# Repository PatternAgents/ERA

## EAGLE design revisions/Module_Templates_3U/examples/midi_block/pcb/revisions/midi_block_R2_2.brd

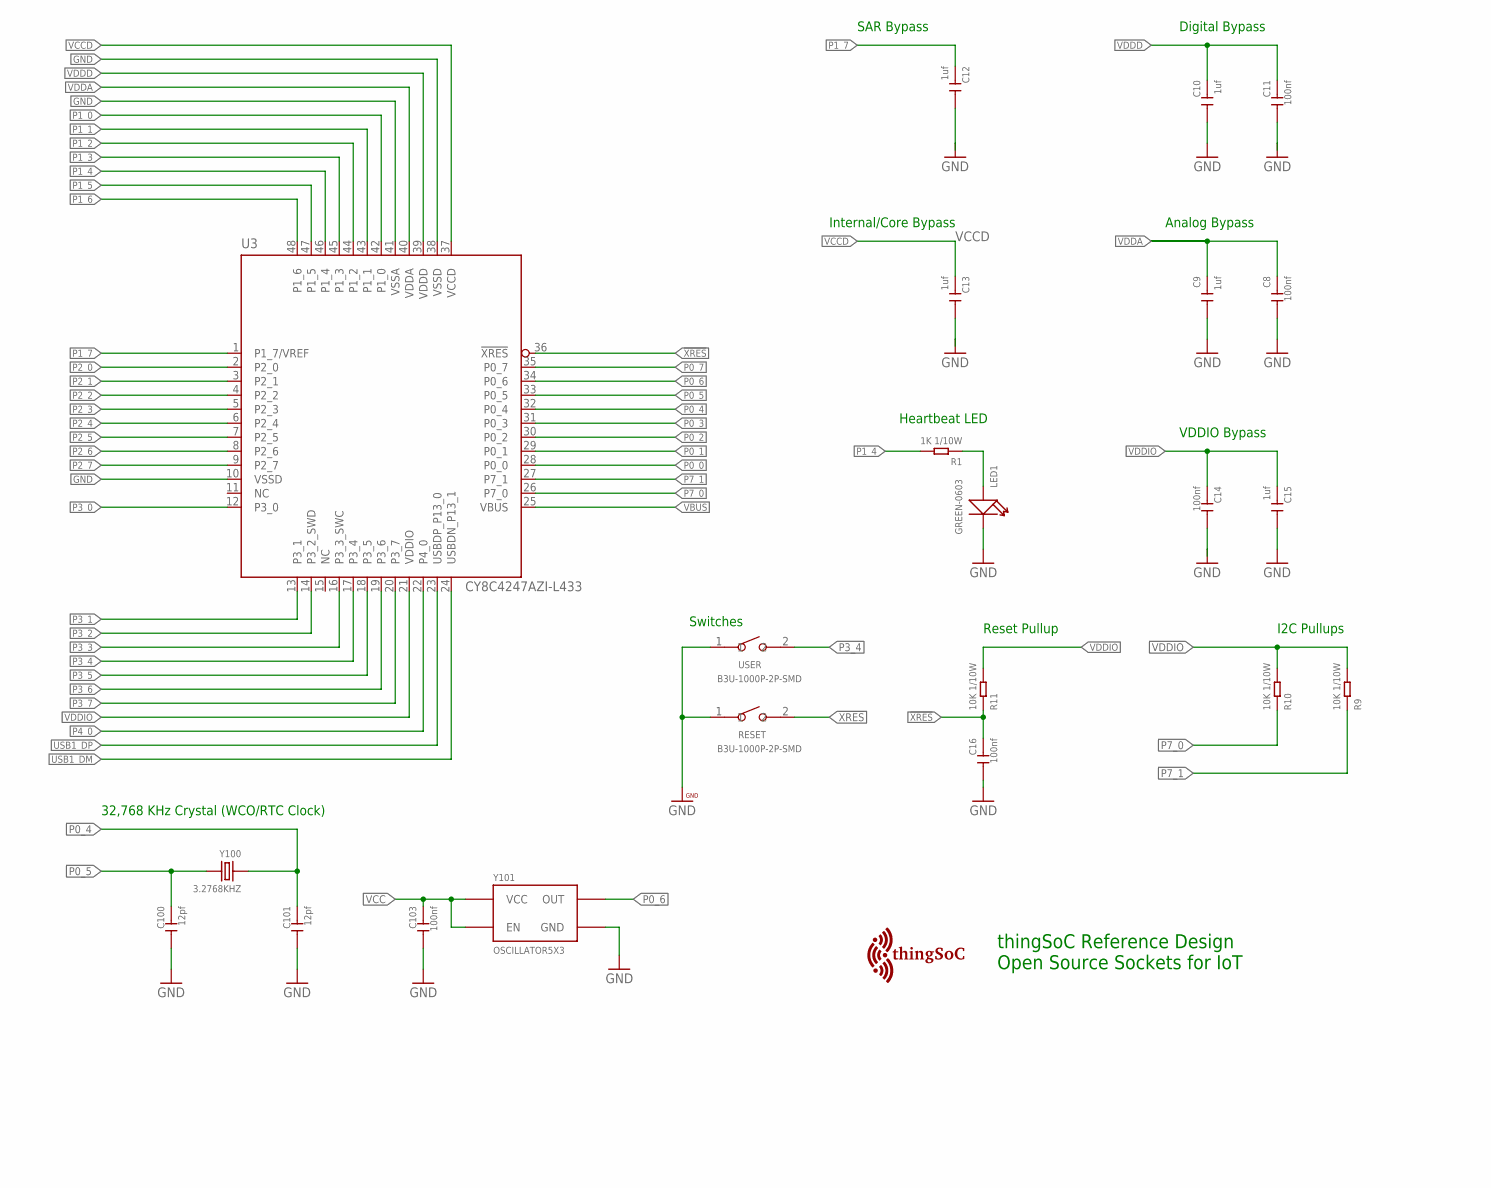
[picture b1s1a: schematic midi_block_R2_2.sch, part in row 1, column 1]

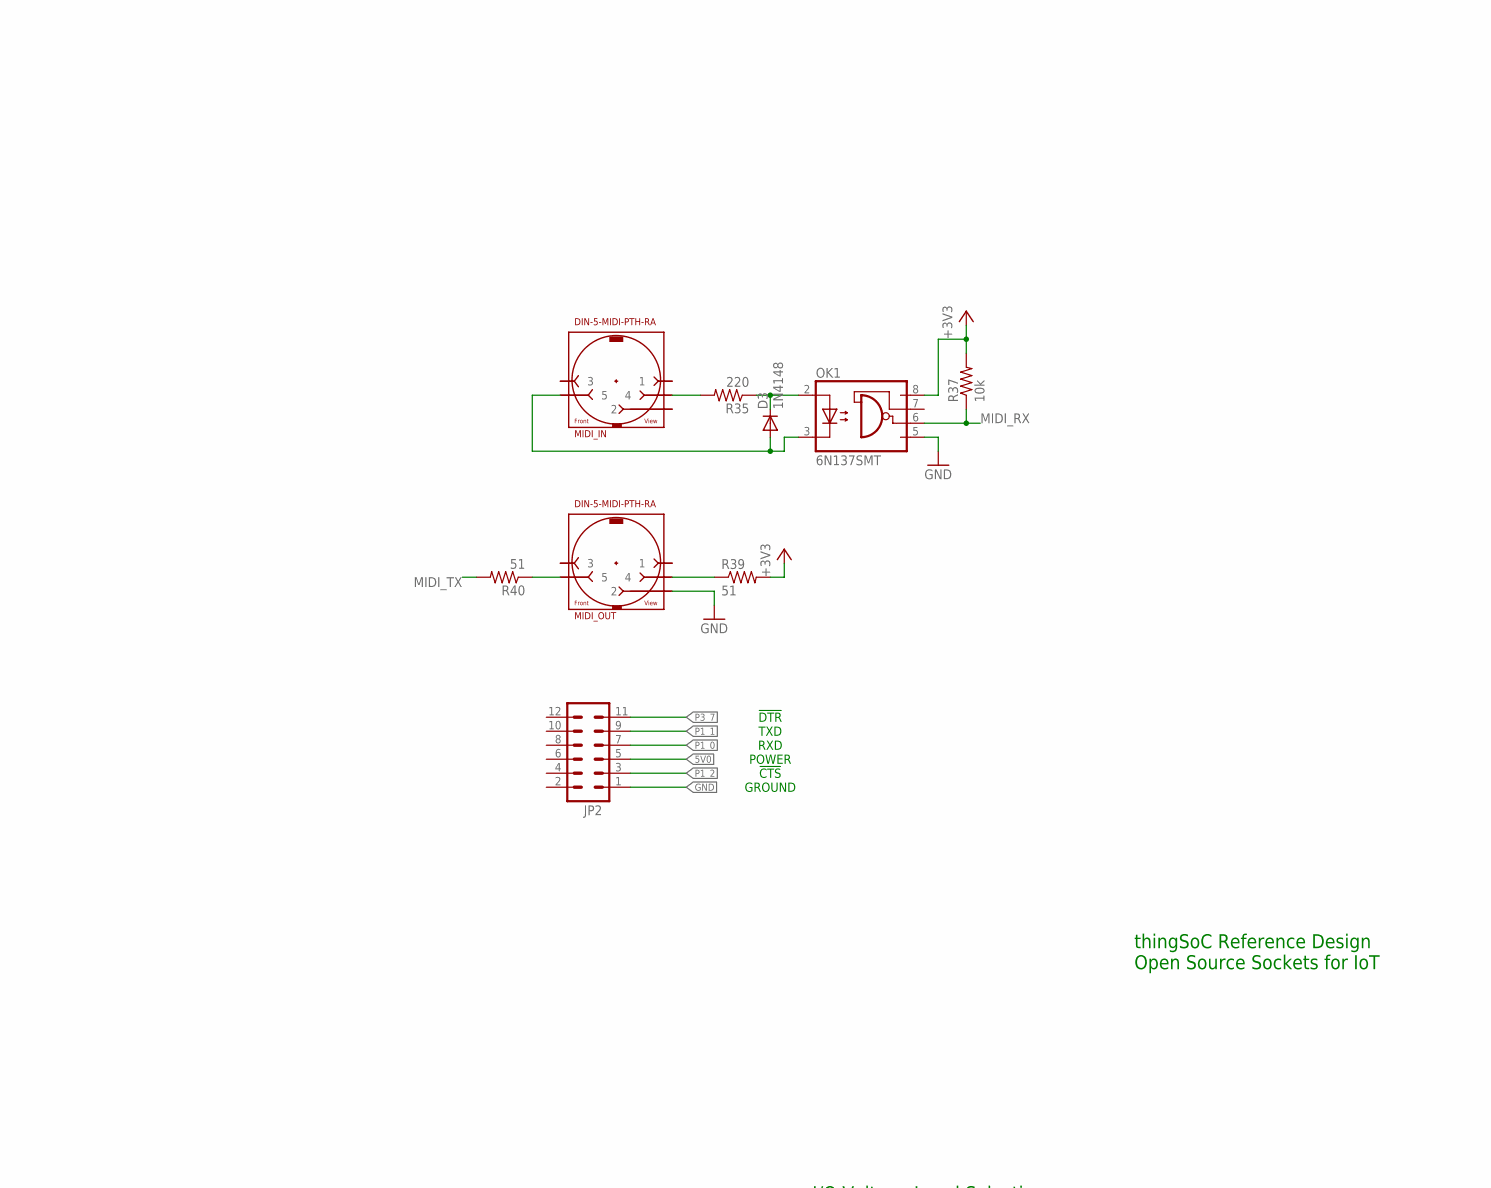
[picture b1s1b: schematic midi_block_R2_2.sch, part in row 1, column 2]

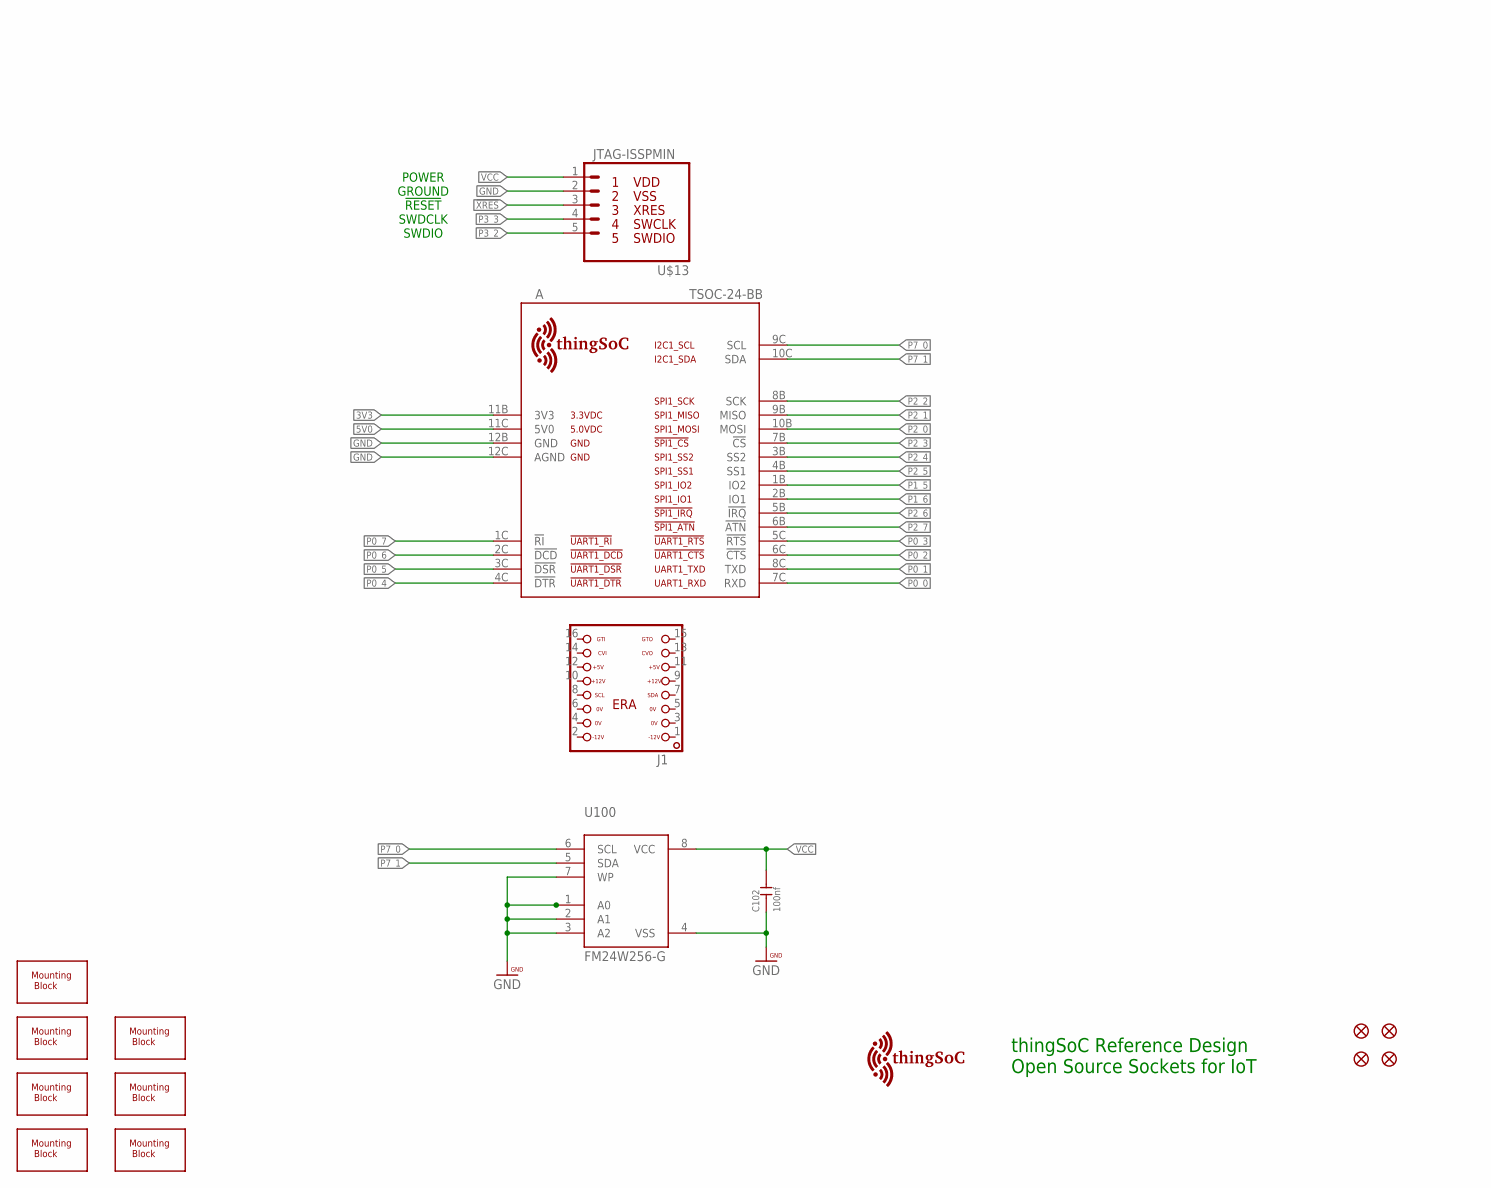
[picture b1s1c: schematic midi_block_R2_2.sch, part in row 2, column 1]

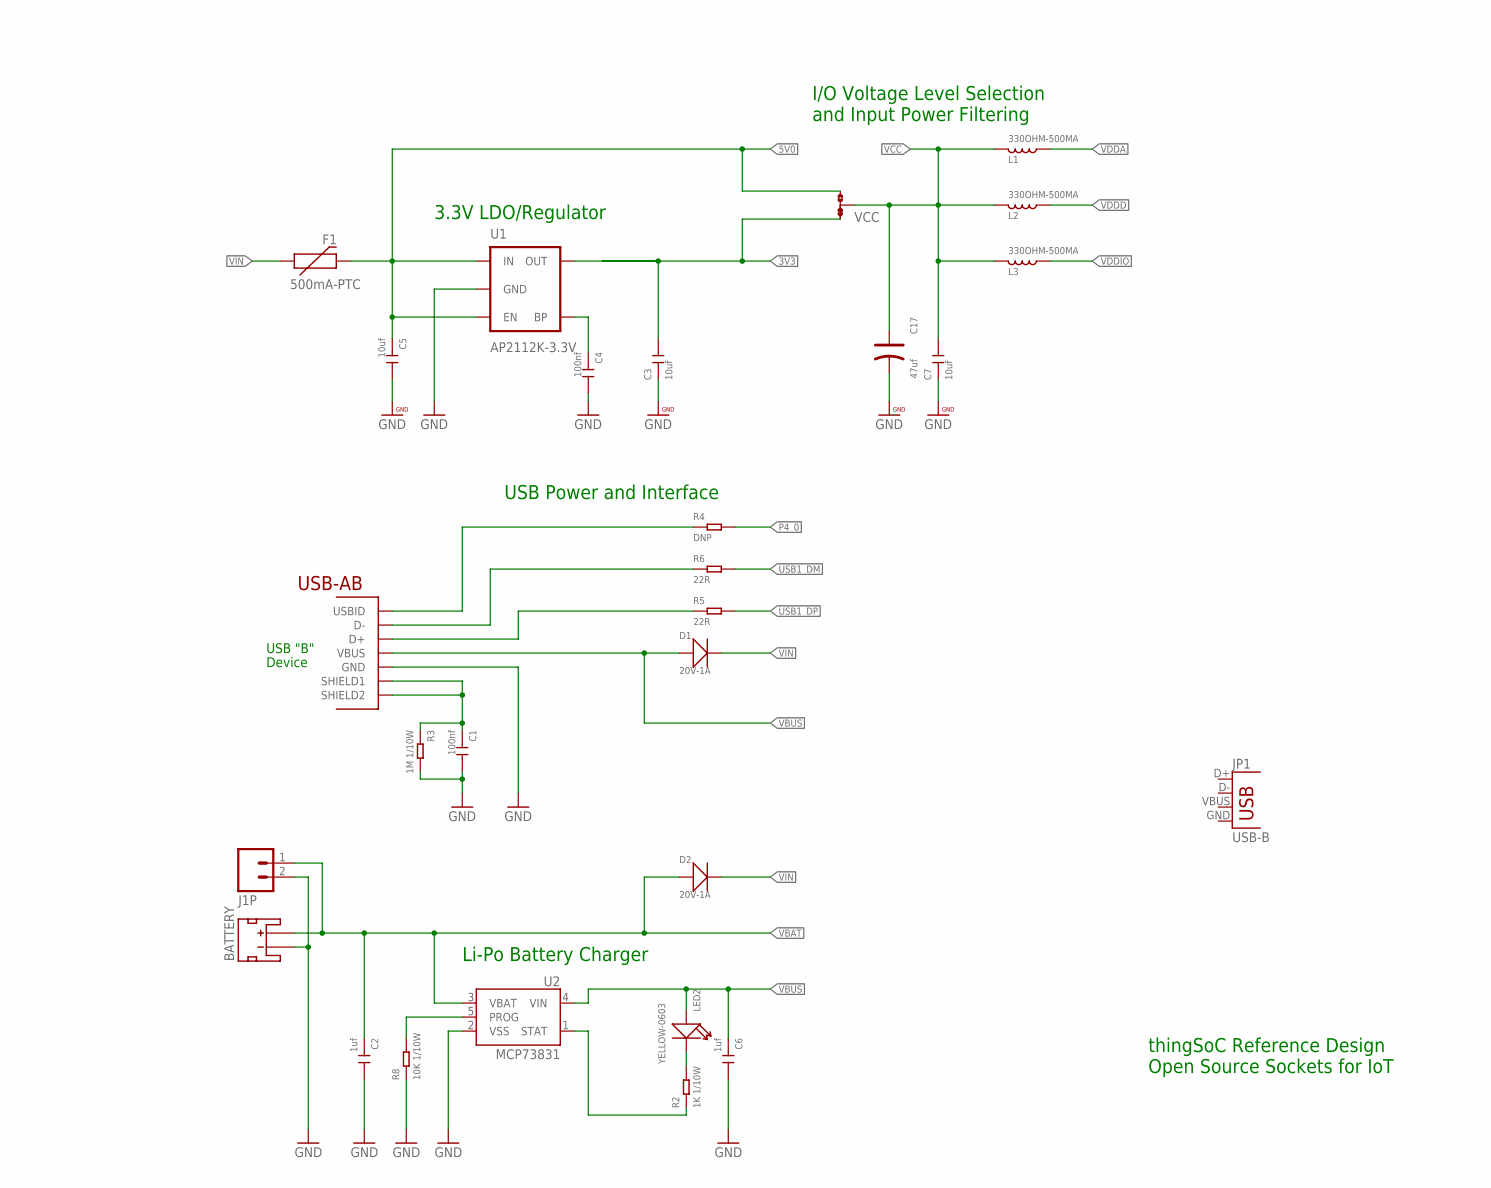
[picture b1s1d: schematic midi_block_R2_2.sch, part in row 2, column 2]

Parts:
A: TSOC-24-BB; TSOC-BB-S24
BATTERY: JST_2MM_MALE; JST-2-SMD
C1, C4, C8, C11, C14, C16, C102, C103: 100nf; C0603
C2, C6, C9, C10, C12, C13, C15: 1uf; C0603
C3, C5, C7: 10uf; C0603
C17: 47uf; AVX-A
C100, C101: 12pf; C0603
D1, D2: 20V-1A; SOD-123
D3: 1N4148; SOD323-W
F1: 500mA-PTC; PTC-1206
FID1, FID2, FID3, FID4: FIDUCIALUFIDUCIAL; MICRO-FIDUCIAL
J1: ERA-SHROUD; ERA
J1P: M02-JST-2-PTH-NO_SILK; JST-2-PTH-NS
JP1: USB-B; USB-B-PTH
JP2: M06X2FEMALE-SMT; 2X6_SMD
L1, L2, L3: 330OHM-500MA; L0603
LED1: GREEN-0603; LED-0603
LED2: YELLOW-0603; LED-0603
MIDI_IN: DIN-5-MIDI-PTH-RA; DIN-5-PTH-RA-SUPPORT
MIDI_OUT: DIN-5-MIDI-PTH-RA; DIN-5-PTH-RA-SUPPORT
OK1: 6N137SMT; DIL8-SMD
R1, R2: 1K 1/10W; R0603
R3: 1M 1/10W; R0603
R4: DNP; R0603
R5, R6: 22R; R0603
R8, R9, R10, R11: 10K 1/10W; R0603
R35: 220; R0603
R37: 10k; R0603
R39, R40: 51; R0603
RESET: B3U-1000P-2P-SMD; SW2-2.6-3.0X2.5X1.2+0.4MM
U1: AP2112K-3.3V; SOT23-5
U2: MCP73831; SOT23-5
U3: CY8C4247AZI-L433; TQFP-7X7-48
U100: FM24W256-G; SO08
U$1, U$7, U$8, U$9, U$10, U$11, U$12: PCB-MB-SIDE; PCB-MB-01-SIDE
U$13: JTAG-ISSPMIN; PSOC_JTAG_MINSILK
U$100: TSOC-LOGO-LRG
U$101: TSOC-LOGO-SMALL; TSOC-LOGO-SML
USB: USB_AB; USB-AB-MICRO-SMD
USER: B3U-1000P-2P-SMD; SW2-2.6-3.0X2.5X1.2+0.4MM
VCC: JMP-3-1_2
Y100: 3.2768KHZ; X2-SMD-L2.0X1.2X0.55MM
Y101: OSCILLATOR5X3; CRYSTAL-SMD-5X3

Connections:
3V3: A.11B (3V3), C3.2, U1.5 (OUT), VCC.1
5V0: A.11C (5V0), C5.1, F1.2, JP2.5, U1.1 (IN), U1.3 (EN), VCC.3
!XRES: C16.1, R11.1, RESET.2, U3.36 (!XRES), U$13.3
+3V3: OK1.8 (VCC), R37.2, R39.2
BYPASS1: C4.1, U1.4 (BP)
CLED: LED2.-, R2.2
CSTAT: R2.1, U2.1 (STAT)
GND: A.12B (GND), A.12C (AGND), BATTERY.1 (-), C1.2, C2.2, C3.1, C4.2, C5.2, C6.2, C7.1, C8.2, C9.2, C10.2, C11.2, C12.2, C13.2, C14.2, C15.2, C16.2, C17.-, C100.2, C101.2, C102.1, C103.2, J1P.2, JP2.1, LED1.-, MIDI_OUT.2, OK1.5 (GND), R3.2, R8.1, RESET.1, U1.2 (GND), U2.2 (VSS), U3.10 (VSSD), U3.38 (VSSD), U3.41 (VSSA), U100.1 (A0), U100.2 (A1), U100.3 (A2), U100.4 (VSS), U100.7 (WP), U$13.2, USB.GND, USER.1, Y101.2 (GND)
MIDI_RX: OK1.6 (VO), R37.1
MIDI_TX: R40.2
unnamed: R8.2, U2.5 (PROG)
unnamed: D3.C, OK1.2 (A), R35.1
unnamed: MIDI_IN.4, R35.2
unnamed: MIDI_OUT.5, R40.1
unnamed: D3.A, MIDI_IN.5, OK1.3 (C)
unnamed: MIDI_OUT.4, R39.1
unnamed: LED1.+, R1.1
P0_0: A.7C (RXD), U3.28 (P0_0)
P0_1: A.8C (TXD), U3.29 (P0_1)
P0_2: A.6C (!CTS), U3.30 (P0_2)
P0_3: A.5C (!RTS), U3.31 (P0_3)
P0_4: A.4C (!DTR), C101.1, U3.32 (P0_4), Y100.1
P0_5: A.3C (!DSR), C100.1, U3.33 (P0_5), Y100.2
P0_6: A.2C (!DCD), U3.34 (P0_6), Y101.3 (OUT)
P0_7: A.1C (!RI), U3.35 (P0_7)
P1_0: JP2.7, U3.42 (P1_0)
P1_1: JP2.9, U3.43 (P1_1)
P1_2: JP2.3, U3.44 (P1_2)
P1_3: U3.45 (P1_3)
P1_4: R1.2, U3.46 (P1_4)
P1_5: A.1B (IO2), U3.47 (P1_5)
P1_6: A.2B (IO1), U3.48 (P1_6)
P1_7: C12.1, U3.1 (P1_7/VREF)
P2_0: A.10B (MOSI), U3.2 (P2_0)
P2_1: A.9B (MISO), U3.3 (P2_1)
P2_2: A.8B (SCK), U3.4 (P2_2)
P2_3: A.7B (!CS), U3.5 (P2_3)
P2_4: A.3B (SS2), U3.6 (P2_4)
P2_5: A.4B (SS1), U3.7 (P2_5)
P2_6: A.5B (!IRQ), U3.8 (P2_6)
P2_7: A.6B (!ATN), U3.9 (P2_7)
P3_0: U3.12 (P3_0)
P3_1: U3.13 (P3_1)
P3_2: U3.14 (P3_2_SWD), U$13.5
P3_3: U3.16 (P3_3_SWC), U$13.4
P3_4: U3.17 (P3_4), USER.2
P3_5: U3.18 (P3_5)
P3_6: U3.19 (P3_6)
P3_7: JP2.11, U3.20 (P3_7)
P4_0: R4.2, U3.22 (P4_0)
P7_0: A.9C (SCL), R10.1, U3.26 (P7_0), U100.6 (SCL)
P7_1: A.10C (SDA), R9.1, U3.27 (P7_1), U100.5 (SDA)
USB1_DM: R6.2, U3.24 (USBDN_P13_1)
USB1_DP: R5.2, U3.23 (USBDP_P13_0)
USB1_I: R4.1, USB.ID (USBID)
USB1_M: R6.1, USB.D-
USB1_P: R5.1, USB.D+
USB1_SHIELD: C1.1, R3.1, USB.SHIELD1, USB.SHIELD2
VBAT: BATTERY.2 (+), C2.1, D2.+, J1P.1, U2.3 (VBAT)
VBUS: C6.1, D1.+, LED2.+, U2.4 (VIN), U3.25 (VBUS), USB.VBUS
VCC: C7.2, C17.+, C102.2, C103.1, L1.1, L2.1, L3.1, U100.8 (VCC), U$13.1, VCC.2, Y101.1 (EN), Y101.4 (VCC)
VCCD: C13.1, U3.37 (VCCD)
VDDA: C8.1, C9.1, L1.2, U3.40 (VDDA)
VDDD: C10.1, C11.1, L2.2, U3.39 (VDDD)
VDDIO: C14.1, C15.1, L3.2, R9.2, R10.2, R11.2, U3.21 (VDDIO)
VIN: D1.-, D2.-, F1.1

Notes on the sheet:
Internal/Core Bypass
Digital Bypass
VDDIO Bypass
SAR Bypass
USB "B"
Device
3.3V LDO/Regulator
Reset Pullup
Heartbeat LED
Analog Bypass
Li-Po Battery Charger
USB Power and Interface
I/O Voltage Level Selection and Input Power Filtering
I2C Pullups
thingSoC Reference Design Open Source Sockets for IoT
!CTS
!DTR
TXD
RXD
POWER
GROUND
Switches
32,768 KHz Crystal (WCO/RTC Clock)
!RESET
SWDCLK
SWDIO

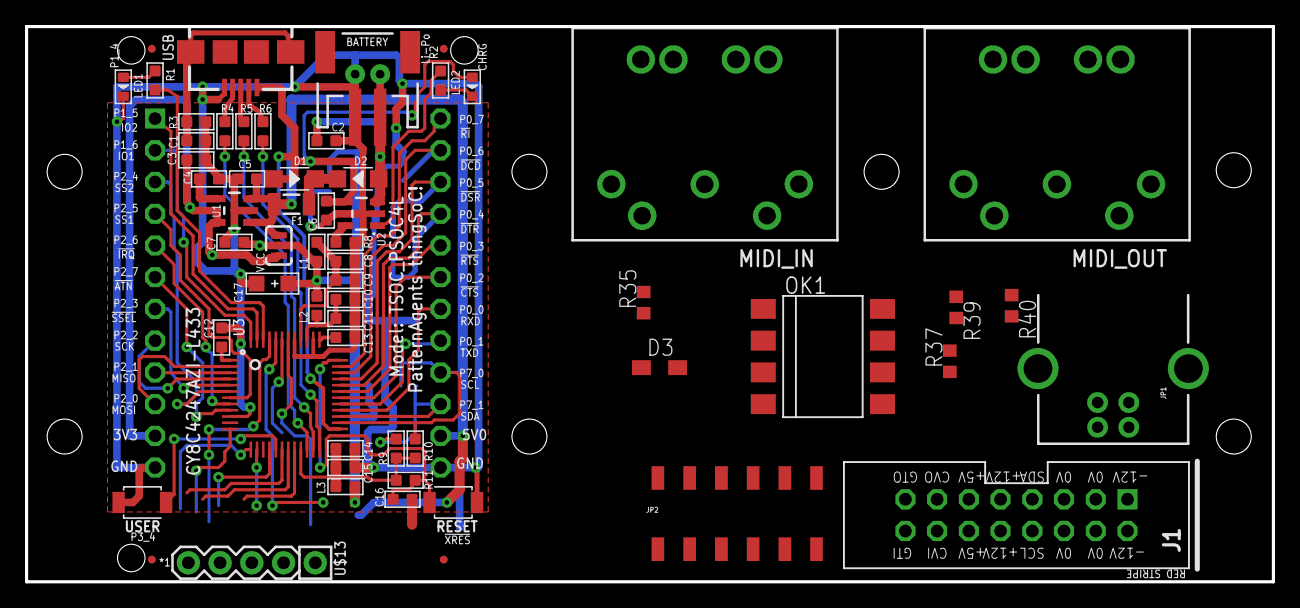
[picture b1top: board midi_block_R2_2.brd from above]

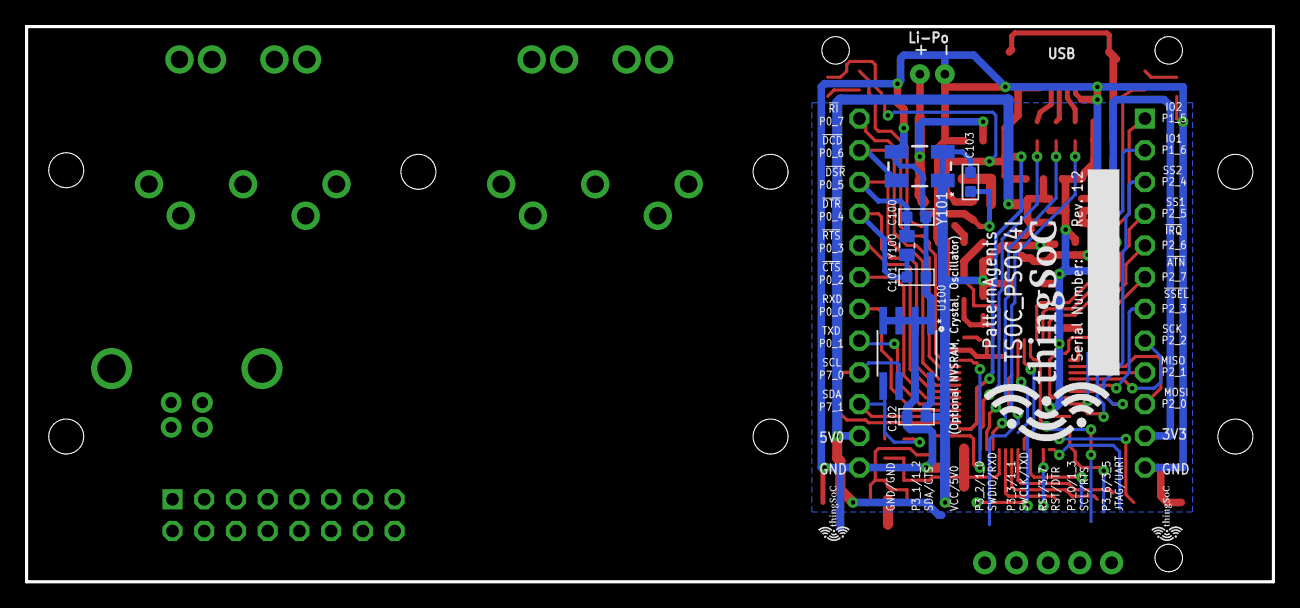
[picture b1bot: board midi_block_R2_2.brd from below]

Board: 2 copper layers, 99.8 x 44.5 mm, 78 parts (11 on the bottom side), 60 nets.

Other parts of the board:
U$102: TSOC-LOGO-SMALL; TSOC-LOGO-SML

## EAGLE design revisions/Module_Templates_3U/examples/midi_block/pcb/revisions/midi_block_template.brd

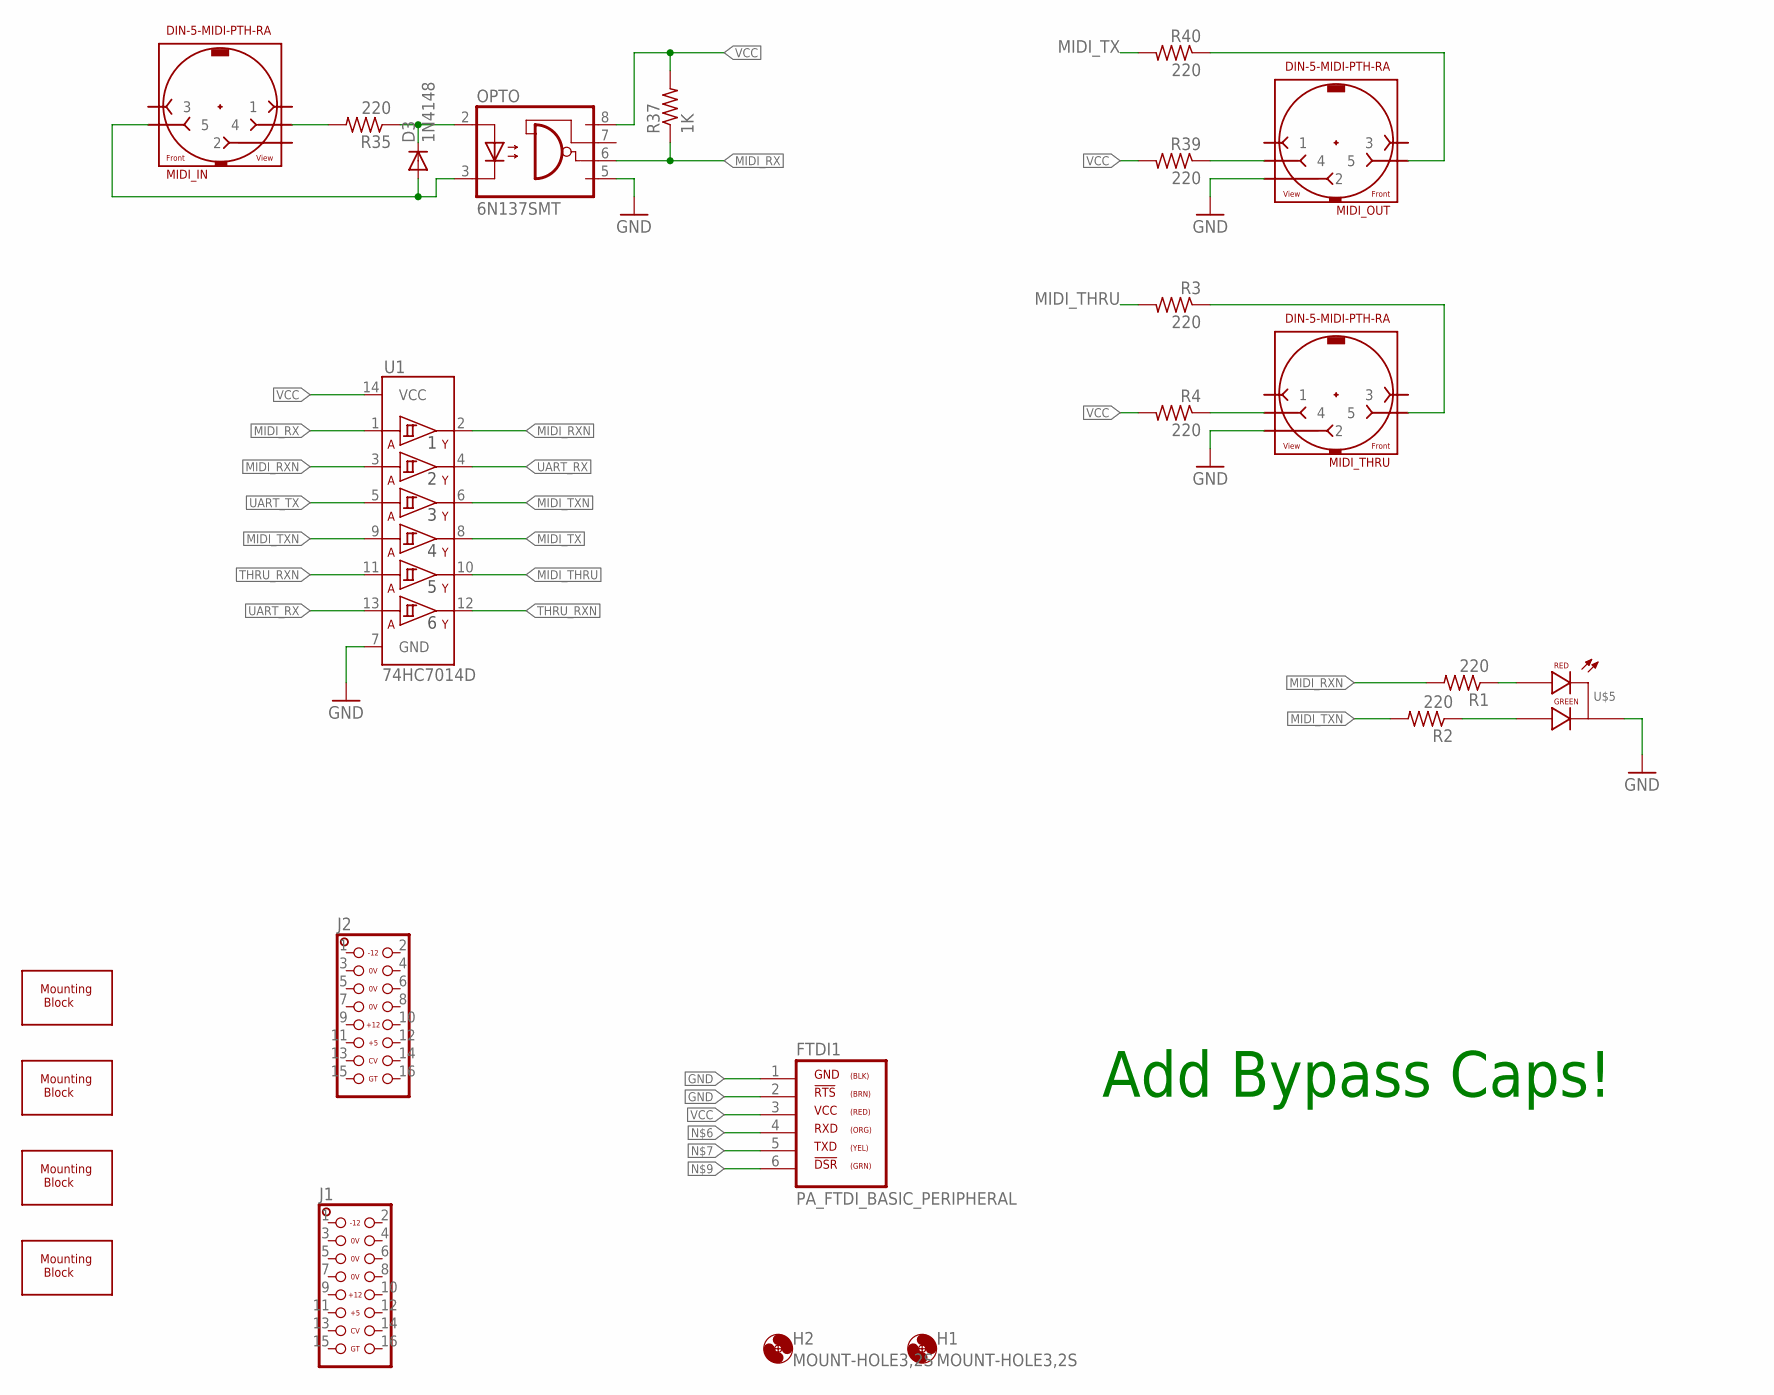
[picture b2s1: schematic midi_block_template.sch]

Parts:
D3: 1N4148; SOD323-W
FTDI1: PA_FTDI_BASIC_PERIPHERAL; PA_PMOD_SIL_MALE
H1, H2: MOUNT-HOLE3,2S; 3,2,SMALL
J1, J2: EUROPWR_2X08-SHROUD; 2X08_EUROPWR_SHROUD
MIDI_IN: DIN-5-MIDI-PTH-RA; DIN-5-PTH-RA-SUPPORT
MIDI_OUT: DIN-5-MIDI-PTH-RA; DIN-5-PTH-RA-SUPPORT
MIDI_THRU: DIN-5-MIDI-PTH-RA; DIN-5-PTH-RA-SUPPORT
OPTO: 6N137SMT; DIL8-SMD
R1, R2, R3, R4, R35, R39, R40: 220; R0603
R37: 1K; R0603
U1: 74HC7014D; SOIC-14
U$1, U$2, U$3, U$4: PCB-MB-SIDE; PCB-MB-01-SIDE
U$5: LED-RG-CC-PTH-G18500; LED-RG-PANEL

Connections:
CL_IN: MIDI_IN.4, R35.2
GND: FTDI1.1, FTDI1.2, MIDI_OUT.2, MIDI_THRU.2, OPTO.5 (GND), U1.7 (GND), U$5.CC (CATHODE)
MIDI_IN: D3.A, MIDI_IN.5, OPTO.3 (C)
MIDI_OUT: MIDI_OUT.5, R40.1
MIDI_OUT1: MIDI_THRU.5, R3.1
MIDI_RX: OPTO.6 (VO), R37.1, U1.1 (1A)
MIDI_RXN: R1.2, U1.2 (1Y), U1.3 (2A)
MIDI_THRU: R3.2, U1.10 (5Y)
MIDI_TX: R40.2, U1.8 (4Y)
MIDI_TXN: R2.2, U1.6 (3Y), U1.9 (4A)
unnamed: R1.1, U$5.RED (RED_CATHODE)
unnamed: R2.1, U$5.GREEN (GREEN_CATHODE)
unnamed: MIDI_THRU.4, R4.1
unnamed: D3.C, OPTO.2 (A), R35.1
unnamed: MIDI_OUT.4, R39.1
THRU_RXN: U1.11 (5A), U1.12 (6Y)
UART_RX: U1.4 (2Y), U1.13 (6A)
UART_TX: U1.5 (3A)
VCC: FTDI1.3, OPTO.8 (VCC), R4.2, R37.2, R39.2, U1.14 (VCC)

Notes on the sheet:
Add Bypass Caps!

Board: 2 copper layers, 24 parts (0 on the bottom side), 18 nets, no tracks yet.

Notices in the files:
parts and their libraries:
thingSoC: License : http://creativecommons.org/licenses/by-sa/4.0
(Creative Commons 4.0)
PatternAgents-Cypress: License : http://creativecommons.org/licenses/by-sa/3.0
(Creative Commons 3.0)
PatternAgents-Interface: Source License : http://www.digilentinc.com/Pmods/licensing.cfm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
